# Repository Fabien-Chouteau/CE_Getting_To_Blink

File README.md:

# CE_Getting_To_Blink
This is my version of the Getting to Blinky board from Contextual Electronic video series.

https://contextualelectronics.com/learning/getting-to-blinky-4-0/

test

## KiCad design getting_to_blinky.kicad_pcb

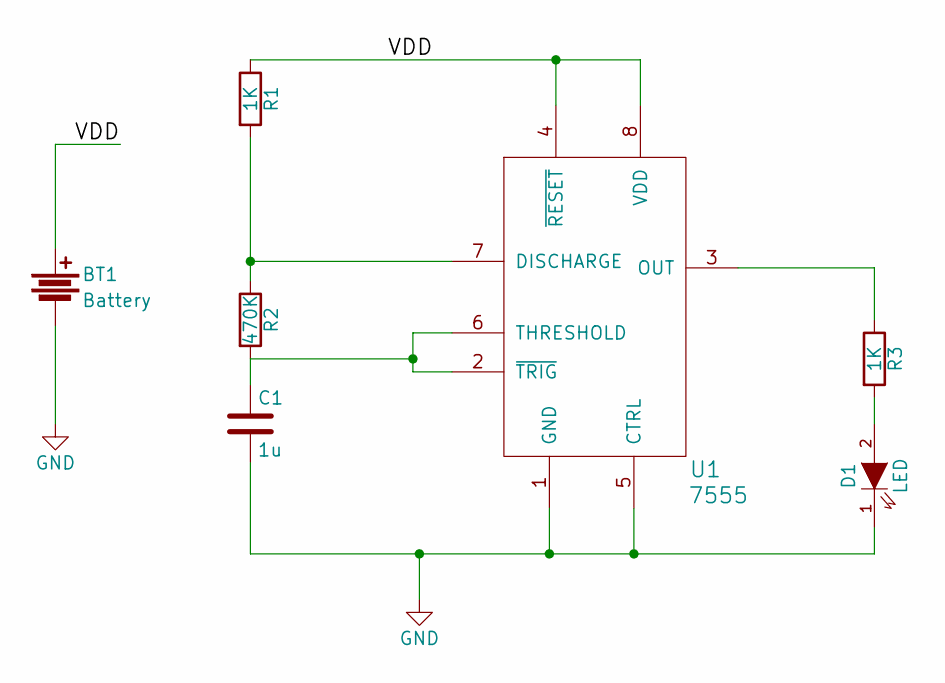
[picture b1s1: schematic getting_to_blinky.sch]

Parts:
BT1: Battery; BatteryHolder
C1: 1u; C_1206_HandSoldering
D1: LED; LED_0805
R1, R3: 1K; R_0805_HandSoldering
R2: 470K; R_0805_HandSoldering
U1: 7555; SOIC-8_3.9x4.9mm_Pitch1.27mm

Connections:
/VDD: BT1.1, R1.1, U1.4 (~RESET), U1.8 (VDD)
GND: BT1.2, C1.2, D1.1 (K), U1.1 (GND), U1.5 (CTRL)
unnamed: C1.1, R2.2, U1.2 (~TRIG), U1.6 (THRESHOLD)
unnamed: D1.2 (A), R3.2
unnamed: R1.2, R2.1, U1.7 (DISCHARGE)
unnamed: R3.1, U1.3 (OUT)

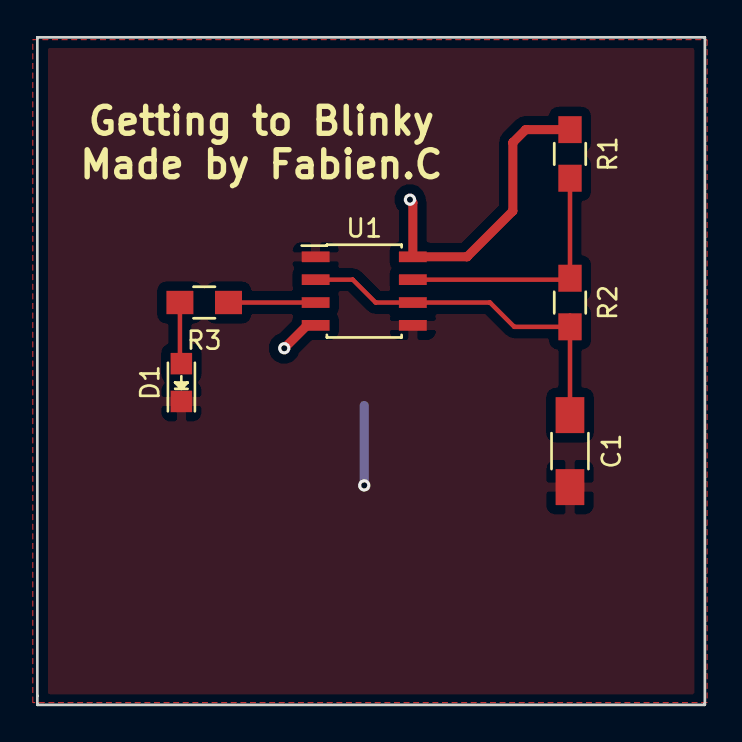
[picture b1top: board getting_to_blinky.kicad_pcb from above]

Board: 2 copper layers, 37.1 x 37.1 mm, 7 parts (1 on the bottom side), 6 nets.

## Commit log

2016-08-20 Add GERBERS and custom part library
2016-08-20 Update README with a link to the videos
2016-10-16 test
